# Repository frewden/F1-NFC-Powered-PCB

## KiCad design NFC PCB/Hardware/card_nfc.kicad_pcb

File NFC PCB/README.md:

\# F1 NFC-Powered PCB

A batteryless Formula 1-inspired PCB designed using KiCad.

\## Features

\- NFC energy harvesting

\- ATtiny1616 microcontroller

\- ST25DV04K NFC IC

\- 15 charlieplexed LEDs

\- Custom NFC antenna

\## Software

\- KiCad 10

\## Author

Vyshnav Harilal

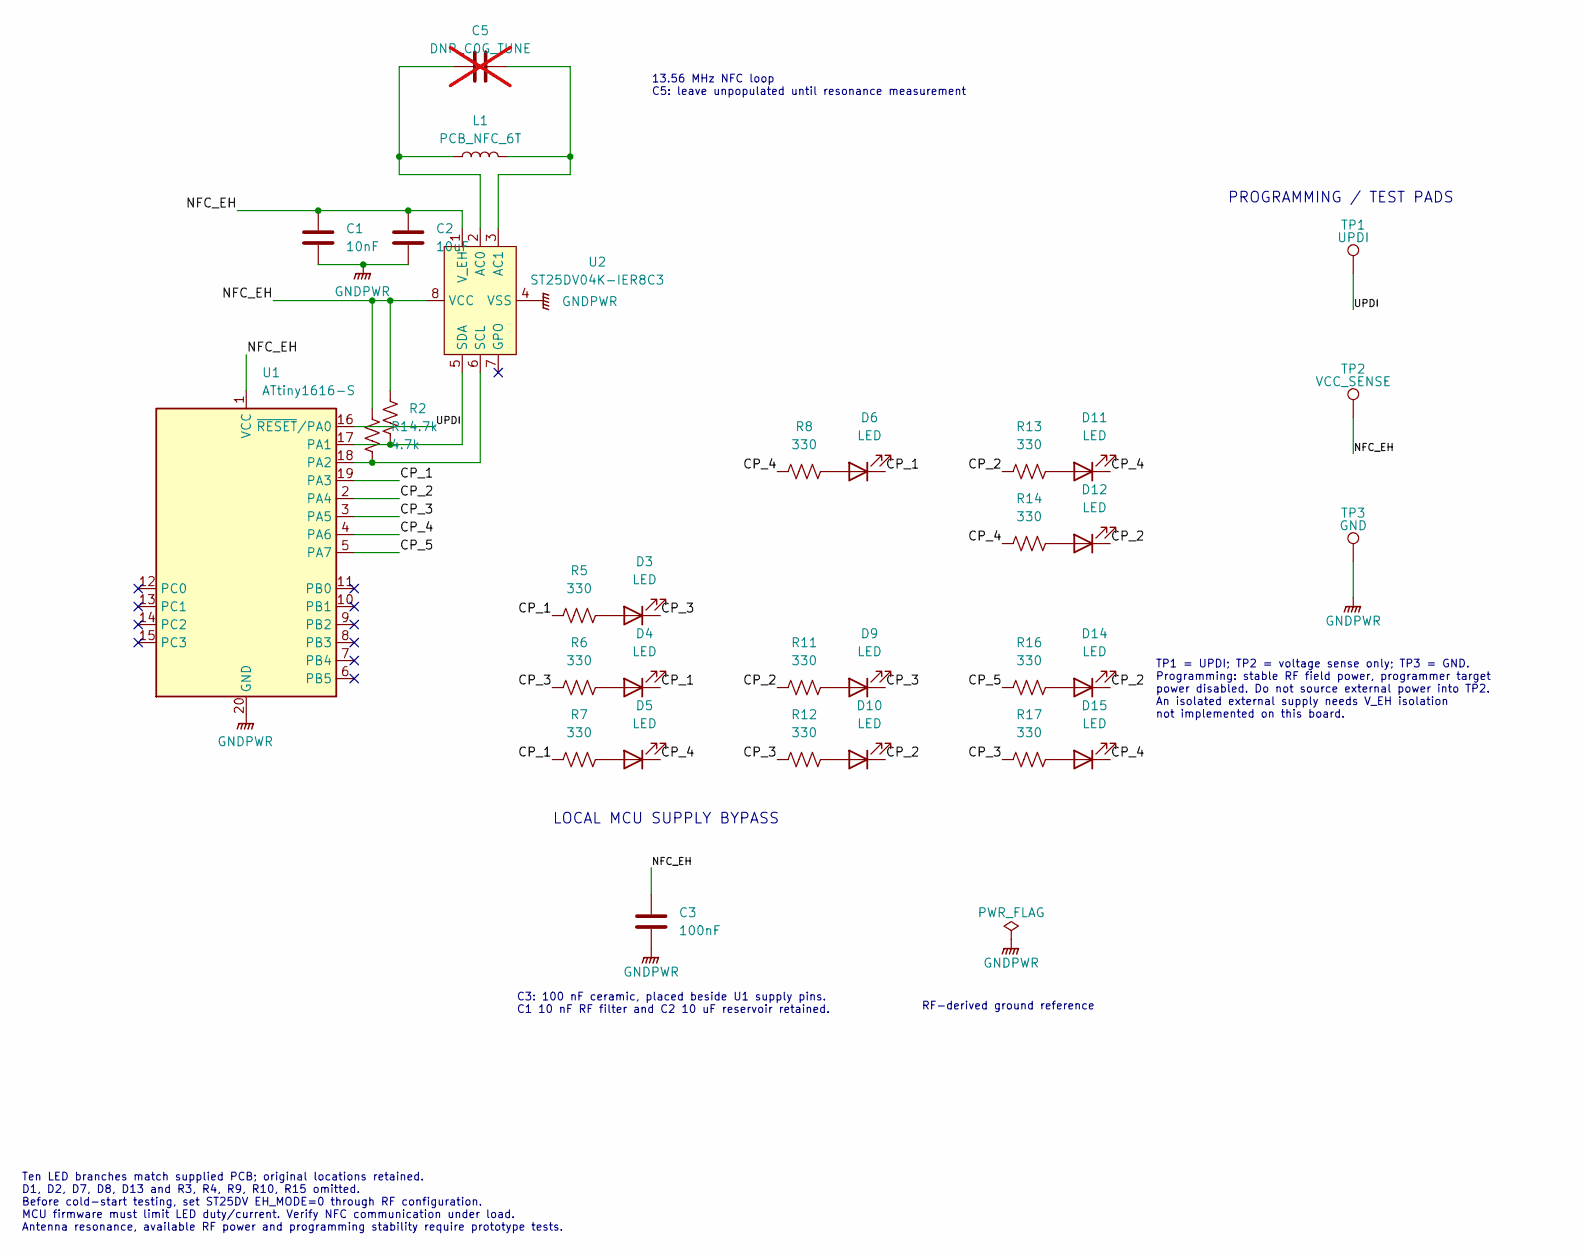
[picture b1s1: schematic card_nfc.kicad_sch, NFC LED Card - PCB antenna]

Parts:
C1: 10nF; C_0603_1608Metric
C2: 10uF; C_0805_2012Metric
C3: 100nF; C_0603_1608Metric
C5: DNP_C0G_TUNE; C_0603_1608Metric; not fitted
D3, D4, D5, D6, D9, D10, D11, D12, D14, D15: LED; LED_0402_1005Metric
L1: PCB_NFC_6T; NFC_Loop_6T
R1, R2: 4.7k; R_0603_1608Metric
R5, R6, R7, R8, R11, R12, R13, R14, R16, R17: 330; R_0603_1608Metric
TP1: UPDI; TestPoint_Pad_D1.5mm
TP2: VCC_SENSE; TestPoint_Pad_D1.5mm
TP3: GND; TestPoint_Pad_D1.5mm
U1: ATtiny1616-S; SOIC-20W_7.5x12.8mm_P1.27mm
U2: ST25DV04K-IER8C3; DFN-8-1EP_3x2mm_P0.5mm_EP1.36x1.46mm

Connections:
/CP_1: D4.1 (K), D6.1 (K), R5.1, R7.1, U1.19 (PA3)
/CP_2: D10.1 (K), D12.1 (K), D14.1 (K), R11.1, R13.1, U1.2 (PA4)
/CP_3: D3.1 (K), D9.1 (K), R6.1, R12.1, R17.1, U1.3 (PA5)
/CP_4: D5.1 (K), D11.1 (K), D15.1 (K), R8.1, R14.1, U1.4 (PA6)
/CP_5: R16.1, U1.5 (PA7)
/NFC_EH: C1.1, C2.1, C3.1, R1.1, R2.1, TP2.1, U1.1 (VCC), U2.1 (V_EH), U2.8 (VCC)
/UPDI: TP1.1, U1.16 (~RESET/PA0)
GNDPWR: C1.2, C2.2, C3.2, TP3.1, U1.20 (GND), U2.4 (VSS)
unnamed: D3.2 (A), R5.2
unnamed: D4.2 (A), R6.2
unnamed: D5.2 (A), R7.2
unnamed: D6.2 (A), R8.2
unnamed: D9.2 (A), R11.2
unnamed: D10.2 (A), R12.2
unnamed: D11.2 (A), R13.2
unnamed: D12.2 (A), R14.2
unnamed: D14.2 (A), R16.2
unnamed: D15.2 (A), R17.2
unnamed: R2.2, U1.17 (PA1), U2.5 (SDA)
unnamed: R1.2, U1.18 (PA2), U2.6 (SCL)
unnamed: C5.1, L1.1, U2.2 (AC0)
unnamed: C5.2, L1.2, U2.3 (AC1)

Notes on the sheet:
LOCAL MCU SUPPLY BYPASS
C3: 100 nF ceramic, placed beside U1 supply pins. C1 10 nF RF filter and C2 10 uF reservoir retained.
13.56 MHz NFC loop C5: leave unpopulated until resonance measurement
PROGRAMMING / TEST PADS
TP1 = UPDI; TP2 = voltage sense only; TP3 = GND. Programming: stable RF field power, programmer target power disabled. Do not source external power into TP2. An isolated external supply needs V_EH isolation not implemented on this board.
Ten LED branches match supplied PCB; original locations retained. D1, D2, D7, D8, D13 and R3, R4, R9, R10, R15 omitted. Before cold-start testing, set ST25DV EH_MODE=0 through RF configuration. MCU firmware must limit LED duty/current. Verify NFC communication under load. Antenna resonance, availab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
RF-derived ground reference

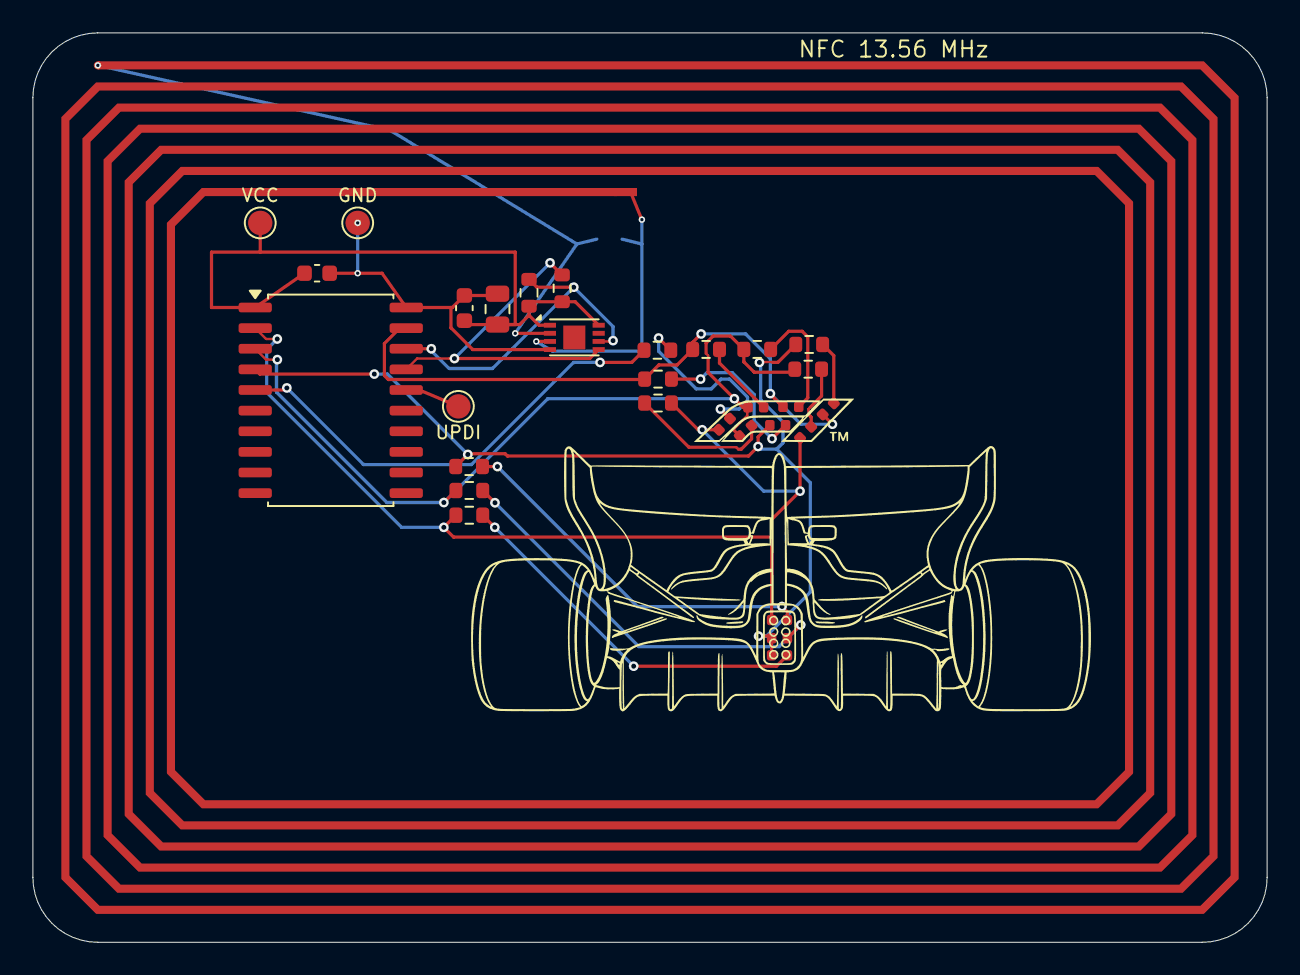
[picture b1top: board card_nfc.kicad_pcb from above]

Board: 2 copper layers, 76.0 x 56.0 mm, 32 parts (1 on the bottom side), 22 nets.
